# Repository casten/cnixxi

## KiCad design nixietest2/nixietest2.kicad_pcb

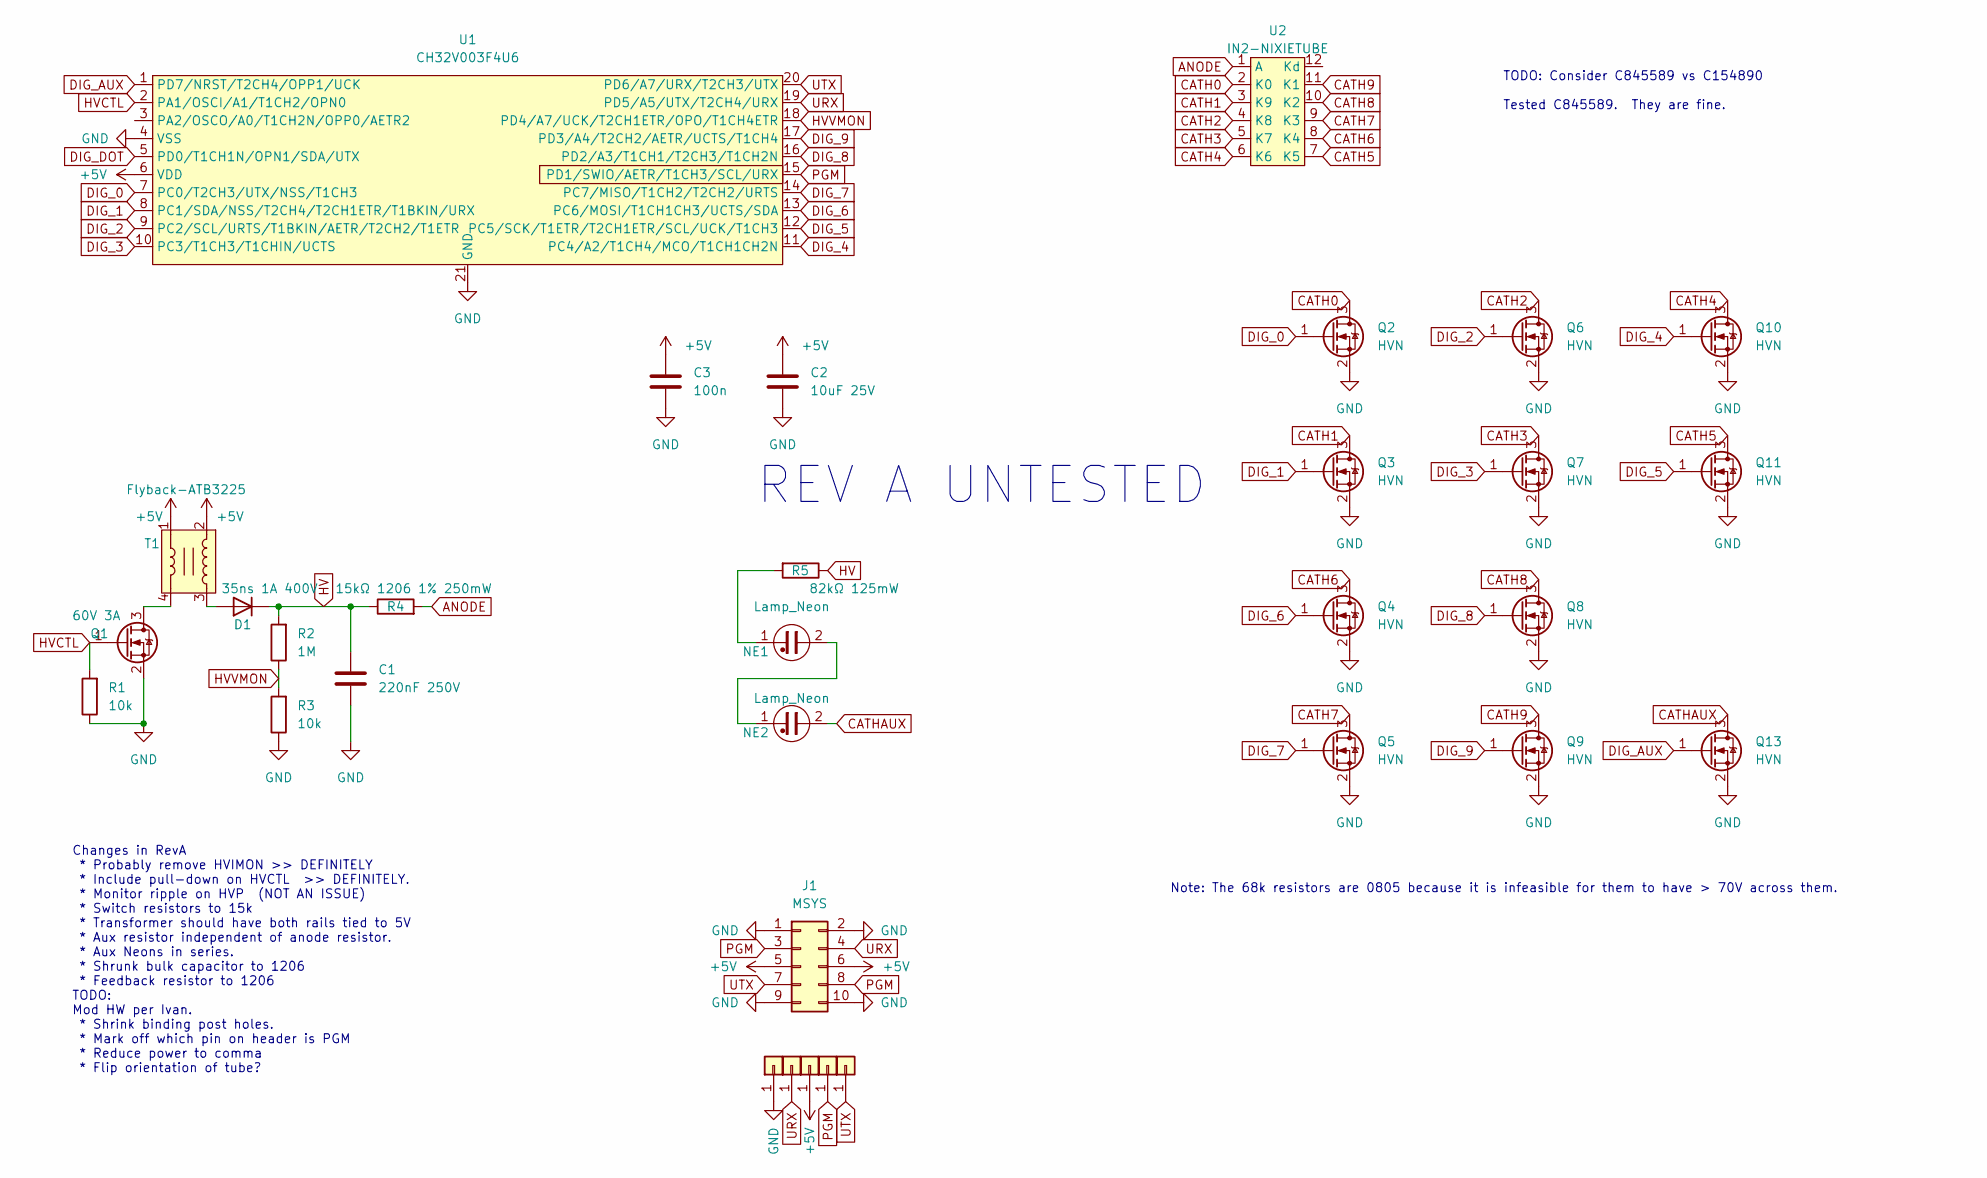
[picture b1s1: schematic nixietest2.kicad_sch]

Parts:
C1: 220nF 250V; C_1206_3216Metric; LCSC C377089
C2: 10uF 25V; C_0603_1608Metric; LCSC C96446
C3: 100n; C_0402_1005Metric; LCSC C1525
D1: 35ns 1A 400V; D_SOD-123F; LCSC C128697
J1: MSYS; PinHeader_2x05_P2.54mm_Horizontal; LCSC C239336
J2, J3, J4, J5, J6: rawpad22
NE1, NE2: Lamp_Neon; neonglow
Q1: 60V 3A; SOT-23; LCSC C2938374
Q2, Q3, Q4, Q5, Q6, Q7, Q8, Q9, Q10, Q11, Q13: HVN; SOT-23; LCSC C845589
R1, R3: 10k; R_0402_1005Metric; LCSC C25744
R2: 1M; R_1206_3216Metric; LCSC C108083
R4: 15kΩ 1206 1% 250mW; R_1206_3216Metric; LCSC C114932
R5: 82kΩ 125mW; R_0805_2012Metric; LCSC C136904
T1: Flyback-ATB3225; LCSC C415291
U1: CH32V003F4U6; QFN-20-1EP_3x3mm_P0.4mm_EP1.65x1.65mm; LCSC C5299908
U2: IN2-NIXIETUBE; IN12-NIXIE

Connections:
+5V: C2.1, C3.1, J1.5, J1.6, J3.1, T1.1, T1.2, U1.6 (VDD)
ANODE: R4.2, U2.1 (A)
CATH0: Q2.3 (D), U2.2 (K0)
CATH1: Q3.3 (D), U2.3 (K9)
CATH2: Q6.3 (D), U2.4 (K8)
CATH3: Q7.3 (D), U2.5 (K7)
CATH4: Q10.3 (D), U2.6 (K6)
CATH5: Q11.3 (D), U2.7 (K5)
CATH6: Q4.3 (D), U2.8 (K4)
CATH7: Q5.3 (D), U2.9 (K3)
CATH8: Q8.3 (D), U2.10 (K2)
CATH9: Q9.3 (D), U2.11 (K1)
CATHAUX: NE2.2, Q13.3 (D)
DIG_0: Q2.1 (G), U1.7 (PC0/T2CH3/UTX/NSS/T1CH3)
DIG_1: Q3.1 (G), U1.8 (PC1/SDA/NSS/T2CH4/T2CH1ETR/T1BKIN/URX)
DIG_2: Q6.1 (G), U1.9 (PC2/SCL/URTS/T1BKIN/AETR/T2CH2/T1ETR)
DIG_3: Q7.1 (G), U1.10 (PC3/T1CH3/T1CHIN/UCTS)
DIG_4: Q10.1 (G), U1.11 (PC4/A2/T1CH4/MCO/T1CH1CH2N)
DIG_5: Q11.1 (G), U1.12 (PC5/SCK/T1ETR/T2CH1ETR/SCL/UCK/T1CH3)
DIG_6: Q4.1 (G), U1.13 (PC6/MOSI/T1CH1CH3/UCTS/SDA)
DIG_7: Q5.1 (G), U1.14 (PC7/MISO/T1CH2/T2CH2/URTS)
DIG_8: Q8.1 (G), U1.16 (PD2/A3/T1CH1/T2CH3/T1CH2N)
DIG_9: Q9.1 (G), U1.17 (PD3/A4/T2CH2/AETR/UCTS/T1CH4)
DIG_AUX: Q13.1 (G), U1.1 (PD7/NRST/T2CH4/OPP1/UCK)
DIG_DOT: U1.5 (PD0/T1CH1N/OPN1/SDA/UTX); also elsewhere on the board
GND: C1.2, C2.2, C3.2, J1.1, J1.2, J1.9, J1.10, J2.1, Q1.2 (S), Q2.2 (S), Q3.2 (S), Q4.2 (S), Q5.2 (S), Q6.2 (S), Q7.2 (S), Q8.2 (S), Q9.2 (S), Q10.2 (S), Q11.2 (S), Q13.2 (S), R1.1, R3.1, U1.4 (VSS), U1.21 (GND); also elsewhere on the board
HV: C1.1, D1.1 (K), R2.2, R4.1, R5.1
HVCTL: Q1.1 (G), R1.2, U1.2 (PA1/OSCI/A1/T1CH2/OPN0)
HVVMON: R2.1, R3.2, U1.18 (PD4/A7/UCK/T2CH1ETR/OPO/T1CH4ETR)
unnamed: D1.2 (A), T1.3
unnamed: NE1.1, R5.2
unnamed: NE1.2, NE2.1
unnamed: Q1.3 (D), T1.4
PGM: J1.3, J1.8, J5.1, U1.15 (PD1/SWIO/AETR/T1CH3/SCL/URX)
URX: J1.4, J4.1, U1.19 (PD5/A5/UTX/T2CH4/URX)
UTX: J1.7, J6.1, U1.20 (PD6/A7/URX/T2CH3/UTX)

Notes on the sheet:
TODO: Consider C845589 vs C154890 Tested C845589. They are fine.
Changes in RevA * Probably remove HVIMON >> DEFINITELY * Include pull-down on HVCTL >> DEFINITELY. * Monitor ripple on HVP (NOT AN ISSUE) * Switch resistors to 15k * Transformer should have both rails tied to 5V * Aux resistor independent of anode resistor. * Aux Neons in series. * Shrunk bulk capa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
REV A UNTESTED
Note: The 68k resistors are 0805 because it is infeasible for them to have > 70V across them.

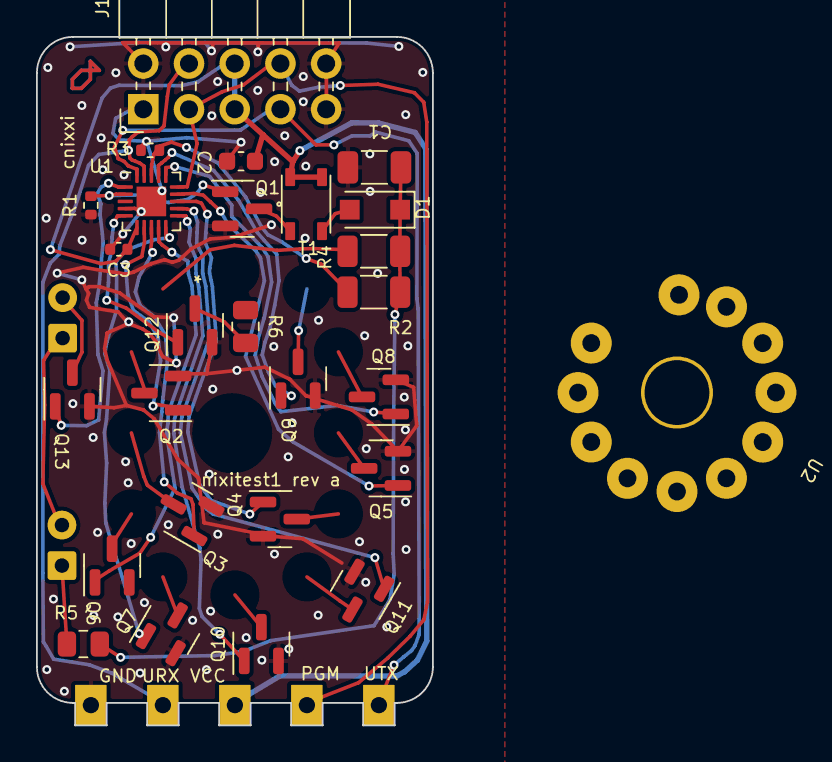
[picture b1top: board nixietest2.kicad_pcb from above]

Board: 2 copper layers, 22.0 x 38.2 mm, 34 parts (0 on the bottom side), 37 nets.

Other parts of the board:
Q12: HVN; SOT-23
R6: 82kΩ 125mW; R_0805_2012Metric

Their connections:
DIG_DOT: Q12.1 (G); also elsewhere on the board
GND: Q12.2 (S); also elsewhere on the board
unnamed: Q12.3 (D), R6.2

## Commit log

2023-05-30 make in2 footprint
